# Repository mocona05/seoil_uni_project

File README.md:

# seoil_uni_project
서일대학 소프트웨어 공학과 C언어 심화 프로젝트 자료실

목적 : ESP32 EV-KIT 모듈을 사용하여 실습 프로젝트 진행

어댑터 PCB 디자인

어댑터 PCB 회로

온습도 표시 웹서버 실행 화면

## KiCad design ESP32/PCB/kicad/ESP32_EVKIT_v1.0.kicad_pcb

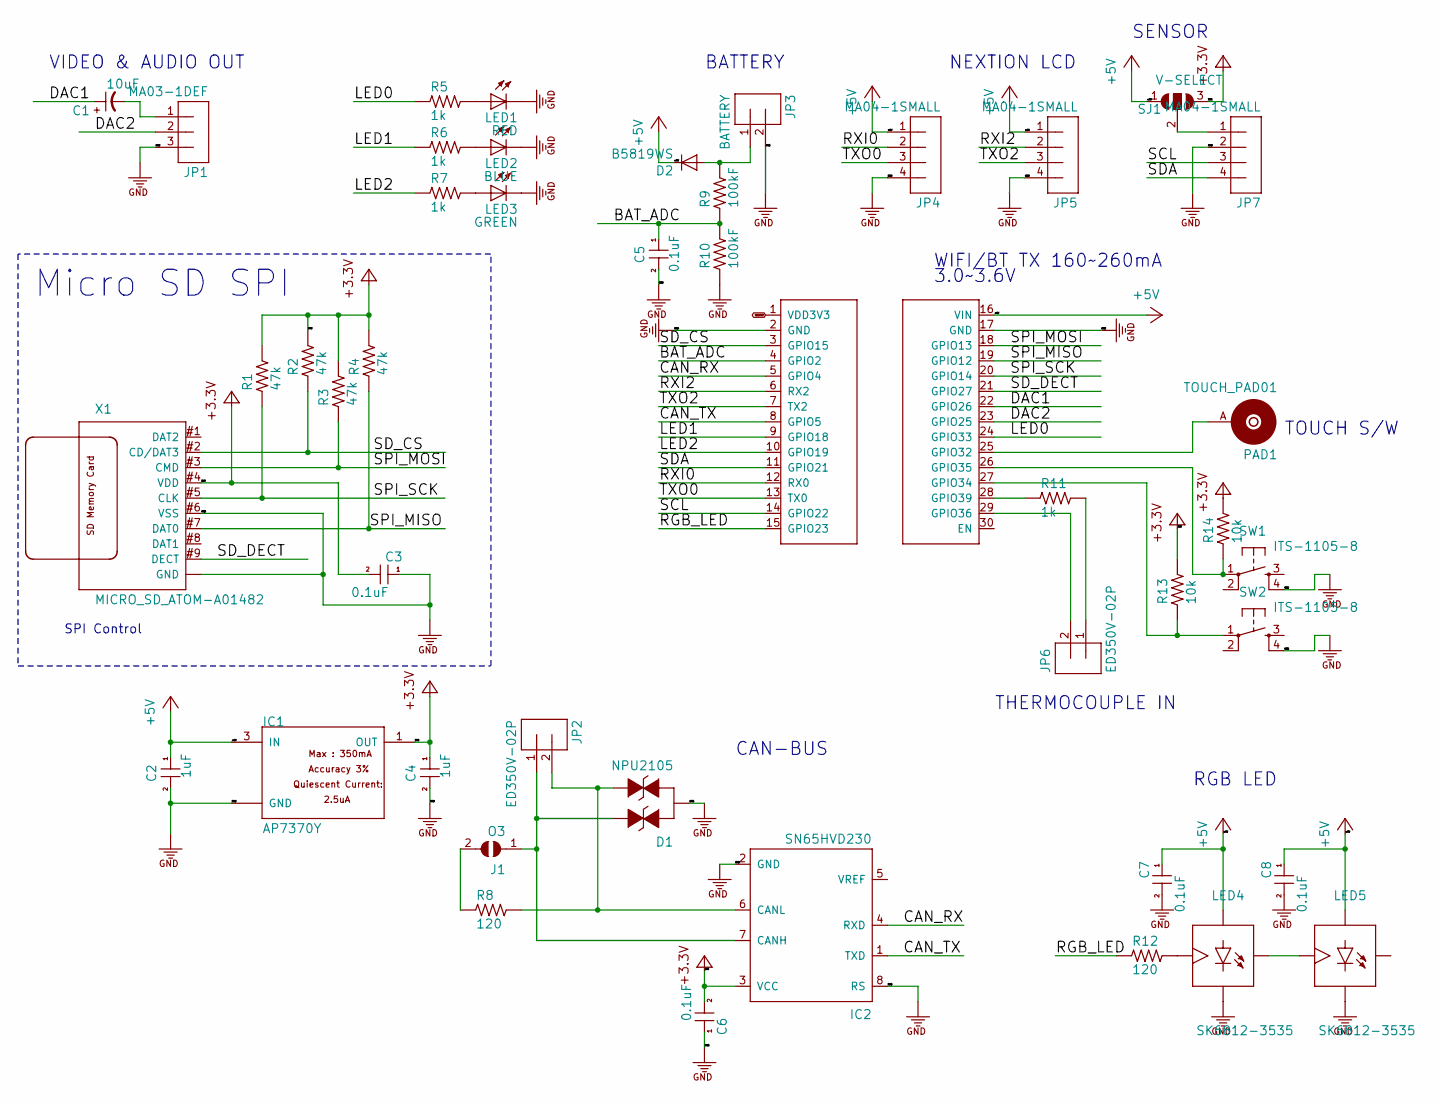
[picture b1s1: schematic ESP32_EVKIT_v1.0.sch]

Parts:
C1: 10uF; C2012_T
C2, C4: 1uF; C0603
C3, C5, C6, C7, C8: 0.1uF; C0603
D1: NPU2105; SOT23@2
D2: B5819WS; SOD323-W
IC1: AP7370Y; SOT89
IC2: SN65HVD230; SO8
J1: O3; SJ
JP1: MA03-1DEF; MA03
JP2, JP6: ED350V-02P
JP3: BATTERY; 53398-02
JP4, JP5, JP7: MA04-1SMALL; MA04-1-S
LED1: RED; LED-1608
LED2: BLUE; LED-1608
LED3: GREEN; LED-1608
LED4, LED5: SK6812-3535; LED3535
M1: ESP32_EVKIT_V1; ESP32_DEVKIT_V1_DOIT
PAD1: TOUCH_PAD01; TOUCH_PAD1
R1, R2, R3, R4: 47k; R0603
R5, R6, R7, R11: 1k; R0603
R8, R12: 120; R0603
R9, R10: 100kF; R0603
R13, R14: 10k; R0603
SJ1: V-SELECT; SJ_3
SW1, SW2: ITS-1105-8; ITS-1105
X1: MICRO_SD_ATOM-A01482; ATOM-A01482

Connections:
3V3: C3.2, C4.1, C6.2, IC1.1 (OUT), IC2.3 (VCC), R1.2, R2.2, R3.2, R4.2, R13.2, R14.2, SJ1.3, X1.#4 (VDD)
+5V: C2.1, C7.1, C8.1, D2.C, IC1.3 (IN), JP4.1, JP5.1, LED4.4 (VDD), LED5.4 (VDD), M1.16 (VIN), SJ1.1
/BAT_ADC: C5.1, M1.4 (GPIO2), R9.1, R10.2
/CAN_RX: IC2.4 (RXD), M1.5 (GPIO4)
/CAN_TX: IC2.1 (TXD), M1.8 (GPIO5)
/DAC1: C1.+, M1.22 (GPIO26)
/DAC2: JP1.2, M1.23 (GPIO25)
/LED0: M1.24 (GPIO33), R5.1
/LED1: M1.9 (GPIO18), R6.1
/LED2: M1.10 (GPIO19), R7.1
/RGB_LED: M1.15 (GPIO23), R12.1
/RXI0: JP4.2, M1.12 (RX0)
/RXI2: JP5.2, M1.6 (RX2)
/SCL: JP7.3, M1.14 (GPIO22)
/SDA: JP7.4, M1.11 (GPIO21)
/SD_CS: M1.3 (GPIO15), R2.1, X1.#2 (CD/DAT3)
/SD_DECT: M1.21 (GPIO27), X1.#9 (DECT)
/SPI_MISO: M1.19 (GPIO12), R4.1, X1.#7 (DAT0)
/SPI_MOSI: M1.18 (GPIO13), R3.1, X1.#3 (CMD)
/SPI_SCK: M1.20 (GPIO14), R1.1, X1.#5 (CLK)
/TXO0: JP4.3, M1.13 (TX0)
/TXO2: JP5.3, M1.7 (TX2)
GND: C2.2, C3.1, C4.2, C5.2, C6.1, C7.2, C8.2, D1.D (PIN3), IC1.2 (GND), IC1.2@1 (GND), IC2.2 (GND), IC2.8 (RS), JP1.3, JP3.2, JP4.4, JP5.4, JP7.2, LED1.C, LED2.C, LED3.C, LED4.2 (VSS), LED5.2 (VSS), M1.2 (GND), M1.17 (GND), R10.1, SW1.4, SW2.4, X1.#6 (VSS), X1.#10 (GND), X1.#10@ (GND), X1.#10@1 (GND), X1.#13 (GND)
unnamed: C1.-, JP1.1
unnamed: D1.G (PIN1), IC2.7 (CANH), J1.1, JP2.1
unnamed: D1.S (PIN2), IC2.6 (CANL), JP2.2, R8.2
unnamed: D2.A, JP3.1, R9.2
unnamed: J1.2, R8.1
unnamed: JP6.1, R11.2
unnamed: JP6.2, M1.29 (GPIO36)
unnamed: JP7.1, SJ1.2
unnamed: LED1.A, R5.2
unnamed: LED2.A, R6.2
unnamed: LED3.A, R7.2
unnamed: LED4.1 (DOUT), LED5.3 (DIN)
unnamed: LED4.3 (DIN), R12.2
unnamed: M1.25 (GPIO32), PAD1.A
unnamed: M1.26 (GPIO35), R14.1, SW1.1
unnamed: M1.27 (GPIO34), R13.1, SW2.1
unnamed: M1.28 (GPIO39), R11.1
VDD3V3: M1.1 (VDD3V3)

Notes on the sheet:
3.0~~3.6V
WIFI/BT TX 160~~260mA
Micro SD SPI
SPI Control
VIDEO & AUDIO OUT
NEXTION LCD
SENSOR
TOUCH S/W
RGB LED
CAN-BUS
BATTERY
THERMOCOUPLE IN

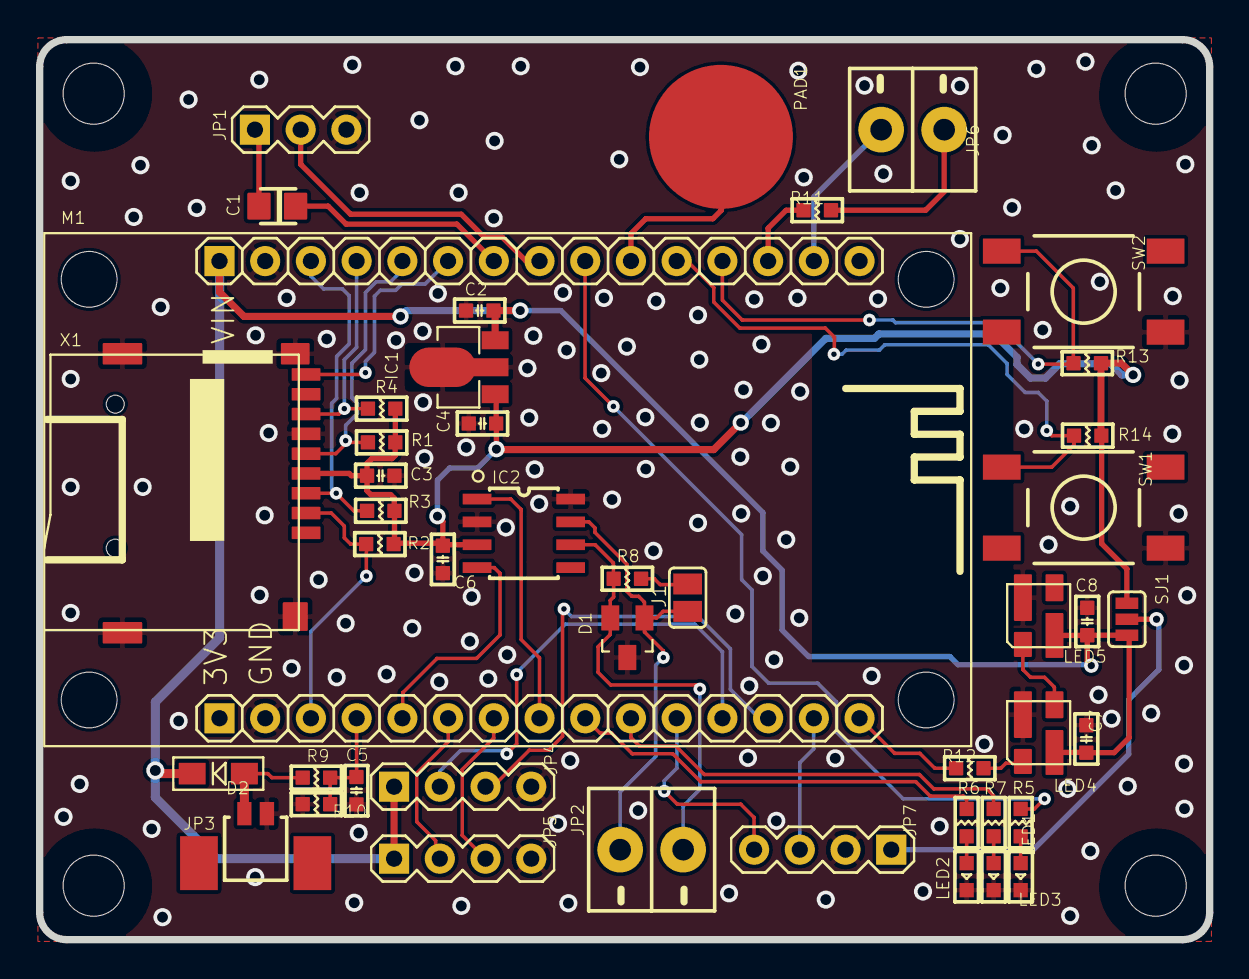
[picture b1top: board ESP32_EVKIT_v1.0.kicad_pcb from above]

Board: 2 copper layers, 65.0 x 50.0 mm, 49 parts (0 on the bottom side), 40 nets.

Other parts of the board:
@HOLE0, @HOLE1, @HOLE2, @HOLE3: (no value)

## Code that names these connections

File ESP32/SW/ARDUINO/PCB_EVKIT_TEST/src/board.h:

#pragma once

#define LED_BUILTIN_PIN 2
#define LED_RED_PIN     33
#define LED_GREEN_PIN   19
#define LED_BLUE_PIN    18
#define RGB_LED_PIN     23

#define RED_LED_TOGGLE  digitalWrite(LED_RED_PIN, !digitalRead(LED_RED_PIN));
#define GREEN_LED_TOGGLE  digitalWrite(LED_GREEN_PIN, !digitalRead(LED_GREEN_PIN));
#define BLUE_LED_TOGGLE  digitalWrite(LED_BLUE_PIN, !digitalRead(LED_BLUE_PIN));
#define BUILTIN_LED_TOGGLE  digitalWrite(LED_BUILTIN_PIN, !digitalRead(LED_BUILTIN_PIN));


#define BOOT_SW_PIN     0
#define SW1_PIN         34
#define SW2_PIN         35

#define SD_CS_PIN       15
#define SPI2_SCK_PIN     14
#define SPI2_MOSI_PIN    13
#define SPI2_MISO_PIN    12
#define SD_DECT_PIN     27

#define SCL_PIN         22
#define SDA_PIN         21

#define DAC1_PIN        25
#define DAC2_PIN        26

#define BAT_ADC_PIN     15
#define TC_ADC_P_PIN    39
#define TC_ADC_N_PIN    36

#define CAN_RX_PIN      4
#define CAN_TX_PIN      5

#define UART_RXI2_PIN   16
#define UART_TXO2_PIN   17

//#define TOUCH_PIN       32
#define TOUCH_CH1       T9


#define READ_SW1_PIN  (!digitalRead(SW1_PIN))
#define READ_SW2_PIN  (!digitalRead(SW2_PIN))
#define READ_BOOT_SW_PIN  (!digitalRead(BOOT_SW_PIN))

#define BUILTIN_LED_ON  digitalWrite(LED_BUILTIN_PIN,HIGH)
#define BUILTIN_LED_OFF  digitalWrite(LED_BUILTIN_PIN,LOW)
#define RED_LED_ON  digitalWrite(LED_RED_PIN,HIGH)
#define RED_LED_OFF  digitalWrite(LED_RED_PIN,LOW)
#define GREEN_LED_ON  digitalWrite(LED_GREEN_PIN,HIGH)
#define GREEN_LED_OFF  digitalWrite(LED_GREEN_PIN,LOW)
#define BLUE_LED_ON  digitalWrite(LED_BLUE_PIN,HIGH)
#define BLUE_LED_OFF  digitalWrite(LED_BLUE_PIN,LOW)

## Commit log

2020-10-15 자료업로드
2020-10-15 esp32 sd logger arduino sw add
    esp32용 sd logger & html 상태표시 소프트웨어 추가
2020-10-15 datasheet 추가
2020-10-15 온습도 web server 메뉴얼 업로드
2020-10-19 Platformio source upload
    vs code Platformio 용 소드코드 등록
2020-10-19 KICAD 파일 등록
2020-10-25 메뉴얼 업로드
2020-10-26 espressif32 soruce update
2020-10-26 esp32 espressif32 source code upate
    espressif32 의 네이티브 센서 동작 기본소스 led 시간 수정
2020-10-28 아두이노 예제 가져오기 메뉴얼 업로드
2020-10-28 예제 생성 문서2 업로드
2020-10-28 메뉴얼 수정
2020-11-04 수업업로드
2020-11-10 Platform Io 설치메뉴얼 업로드
2020-11-11 예제코드 업로드
2020-11-11 예제코드 및 수업자료 업로드
2020-11-11 드라이버 업로드
2020-11-11 문서자료 업로드 및 드라이버 등록
2020-11-13 platform Io 설치 메뉴얼 업로드
2020-11-13 sd memory source code upload
2020-11-17 PCB TEST CODE UPDATE
2020-11-18 ARDUINO 예제 자료 업로드
2020-11-18 수업전 자료업로드
2020-11-24 예제업로드
2020-11-25 강의전 업로드
2020-11-25 문서다시정리
2020-11-25 11월25일 수업중 작성 예제 업로드
2020-12-02 강의전 업데이트
2020-12-02 자료내용추가
2020-12-02 12월 2일 수업 중 예제 업로드 (BlueTooth_remote)
2020-12-09 수업전 업데이트
2020-12-30 MQTT 테스트 소스 및 문서 등록
2020-12-31 MQTT 예제수정
2021-07-17 notebook change
